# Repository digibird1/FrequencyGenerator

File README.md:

# FrequencyGenerator
Frequency generator based on the LTC9603 Programmable Oscillator and controlled by the ATMEL ATMEGA328 microcontroller (Arduino)
The operation frequency is 1kHz-68MHz

http://www.linear.com/product/LTC6903

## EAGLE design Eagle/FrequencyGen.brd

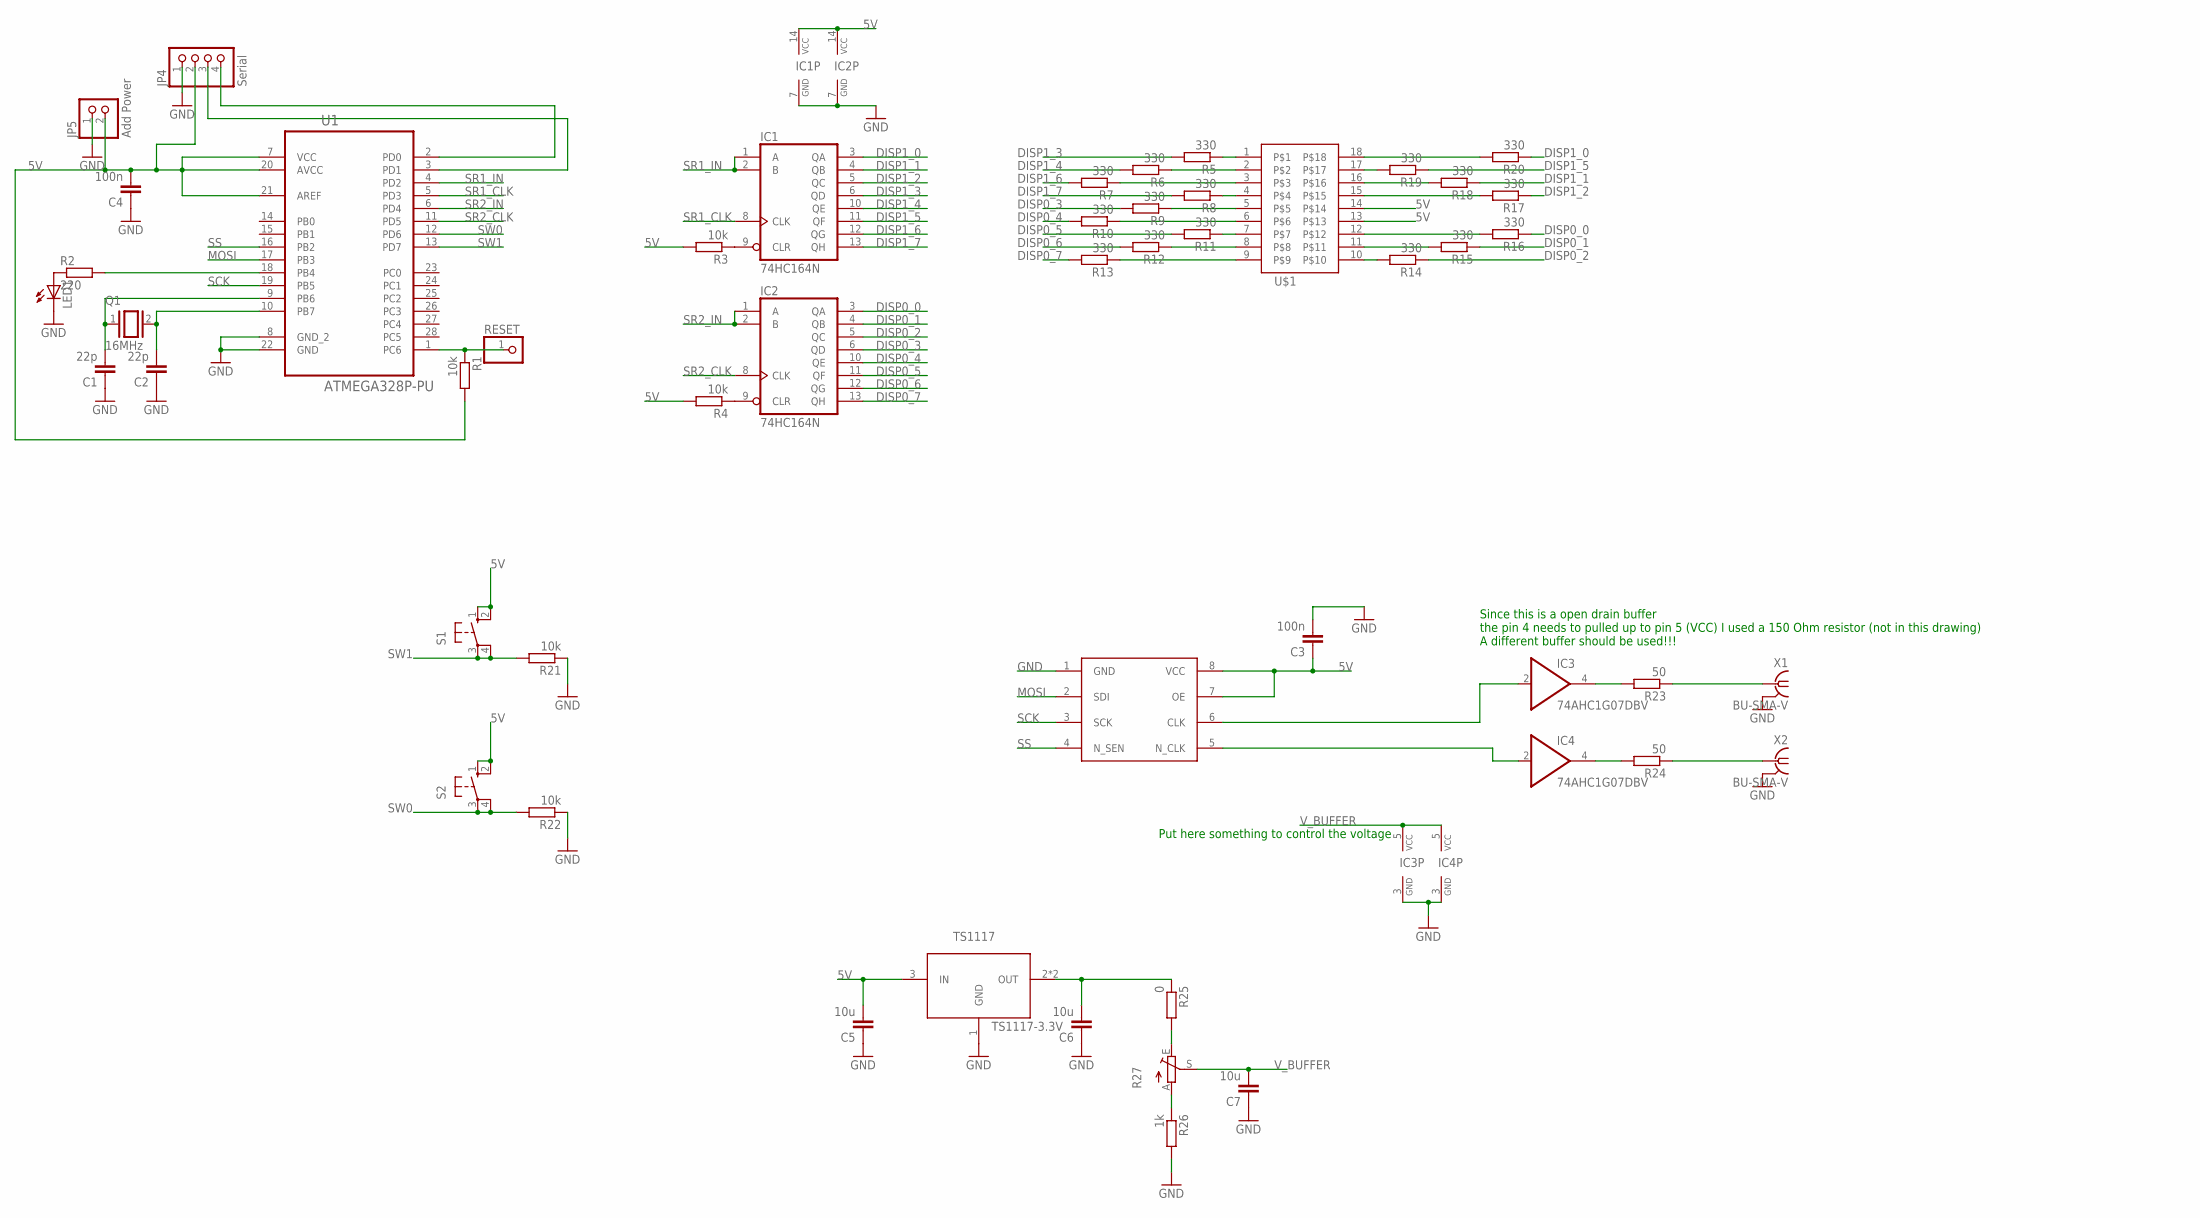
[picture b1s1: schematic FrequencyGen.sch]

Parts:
C1, C2: 22p; C0805
C3, C4: 100n; C0805
C5, C6, C7: 10u; C0805
IC1, IC2: 74HC164N; DIL14
IC3, IC4: 74AHC1G07DBV; SOT23-5
JP4: Serial; 1X04
JP5: Add Power; 1X02
LED1: LED_ELD260; LED_LD260
Q1: 16MHz; QS
R1, R3, R4, R21, R22: 10k; R0805
R2: 220; R0805
R5, R6, R7, R8, R9, R10, R11, R12, R13, R14, R15, R16, R17, R18, R19, R20: 330; R0805
R23, R24: 50; R0805
R25: 0; R0805
R26: 1k; R0805
R27: TRIM_EU-CA6V; CA6V
RESET: PINHD-1X1; 1X01
S1, S2: 10-XX; B3F-10XX
U1: ATMEGA328P-PU; DIP254P762X457-28
U$1: SEG_DISP_2X8; DIL18-6
U$2: LTC6903; MSOP8
U$3: TS1117-3.3V; SOT223
X1, X2: BU-SMA-V

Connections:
5V: C3.1, C4.2, C5.2, IC1.14 (VCC), IC2.14 (VCC), JP4.2, JP5.2, R1.2, R3.2, R4.2, S1.1 (S), S1.2 (S1), S2.1 (S), S2.2 (S1), U1.7 (VCC), U1.20 (AVCC), U1.21 (AREF), U$1.13, U$1.14, U$2.7 (OE), U$2.8 (VCC), U$3.3 (IN)
DISP0_0: IC2.3 (QA), R16.1
DISP0_1: IC2.4 (QB), R15.1
DISP0_2: IC2.5 (QC), R14.1
DISP0_3: IC2.6 (QD), R9.2
DISP0_4: IC2.10 (QE), R10.2
DISP0_5: IC2.11 (QF), R11.2
DISP0_6: IC2.12 (QG), R12.2
DISP0_7: IC2.13 (QH), R13.2
DISP1_0: IC1.3 (QA), R20.1
DISP1_1: IC1.4 (QB), R18.1
DISP1_2: IC1.5 (QC), R17.1
DISP1_3: IC1.6 (QD), R5.2
DISP1_4: IC1.10 (QE), R6.2
DISP1_5: IC1.11 (QF), R19.1
DISP1_6: IC1.12 (QG), R7.2
DISP1_7: IC1.13 (QH), R8.2
GND: C1.1, C2.1, C3.2, C4.1, C5.1, C6.1, C7.1, IC1.7 (GND), IC2.7 (GND), IC3.3 (GND), IC4.3 (GND), JP4.1, JP5.1, LED1.K (C), R21.1, R22.1, R26.2, U1.8 (GND_2), U1.22 (GND), U$2.1 (GND), U$3.1 (GND), X1.2, X1.3 (2), X1.4 (2), X1.5 (2), X2.2, X2.3 (2), X2.4 (2), X2.5 (2)
MOSI: U1.17 (PB3), U$2.2 (SDI)
unnamed: LED1.A, R2.1
unnamed: IC1.9 (CLR), R3.1
unnamed: IC2.9 (CLR), R4.1
unnamed: R5.1, U$1.1
unnamed: R1.1, RESET.1, U1.1 (PC6)
unnamed: C1.2, Q1.1, U1.9 (PB6)
unnamed: C2.2, Q1.2, U1.10 (PB7)
unnamed: R6.1, U$1.2
unnamed: R7.1, U$1.3
unnamed: R8.1, U$1.4
unnamed: R9.1, U$1.5
unnamed: R10.1, U$1.6
unnamed: R11.1, U$1.7
unnamed: R12.1, U$1.8
unnamed: R13.1, U$1.9
unnamed: R20.2, U$1.18
unnamed: R19.2, U$1.17
unnamed: R18.2, U$1.16
unnamed: R17.2, U$1.15
unnamed: R16.2, U$1.12
unnamed: R15.2, U$1.11
unnamed: R14.2, U$1.10
unnamed: R2.2, U1.18 (PB4)
unnamed: JP4.3, U1.3 (PD1)
unnamed: JP4.4, U1.2 (PD0)
unnamed: IC3.4 (O), R23.2
unnamed: IC4.4 (O), R24.2
unnamed: R23.1, X1.1
unnamed: R24.1, X2.1
unnamed: IC3.2 (I), U$2.6 (CLK)
unnamed: IC4.2 (I), U$2.5 (N_CLK)
unnamed: R25.2, R27.E
unnamed: C6.2, R25.1, U$3.2 (OUT), U$3.4 (OUT)
unnamed: R26.1, R27.A
SCK: U1.19 (PB5), U$2.3 (SCK)
SR1_CLK: IC1.8 (CLK), U1.5 (PD3)
SR1_IN: IC1.1 (A), IC1.2 (B), U1.4 (PD2)
SR2_CLK: IC2.8 (CLK), U1.11 (PD5)
SR2_IN: IC2.1 (A), IC2.2 (B), U1.6 (PD4)
SS: U1.16 (PB2), U$2.4 (N_SEN)
SW0: R22.2, S2.3, S2.4 (P1), U1.12 (PD6)
SW1: R21.2, S1.3, S1.4 (P1), U1.13 (PD7)
V_BUFFER: C7.2, IC3.5 (VCC), IC4.5 (VCC), R27.S

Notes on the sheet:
Put here something to control the voltage
Since this is a open drain buffer the pin 4 needs to pulled up to pin 5 (VCC) I used a 150 Ohm resistor (not in this drawing) A different buffer should be used!!!

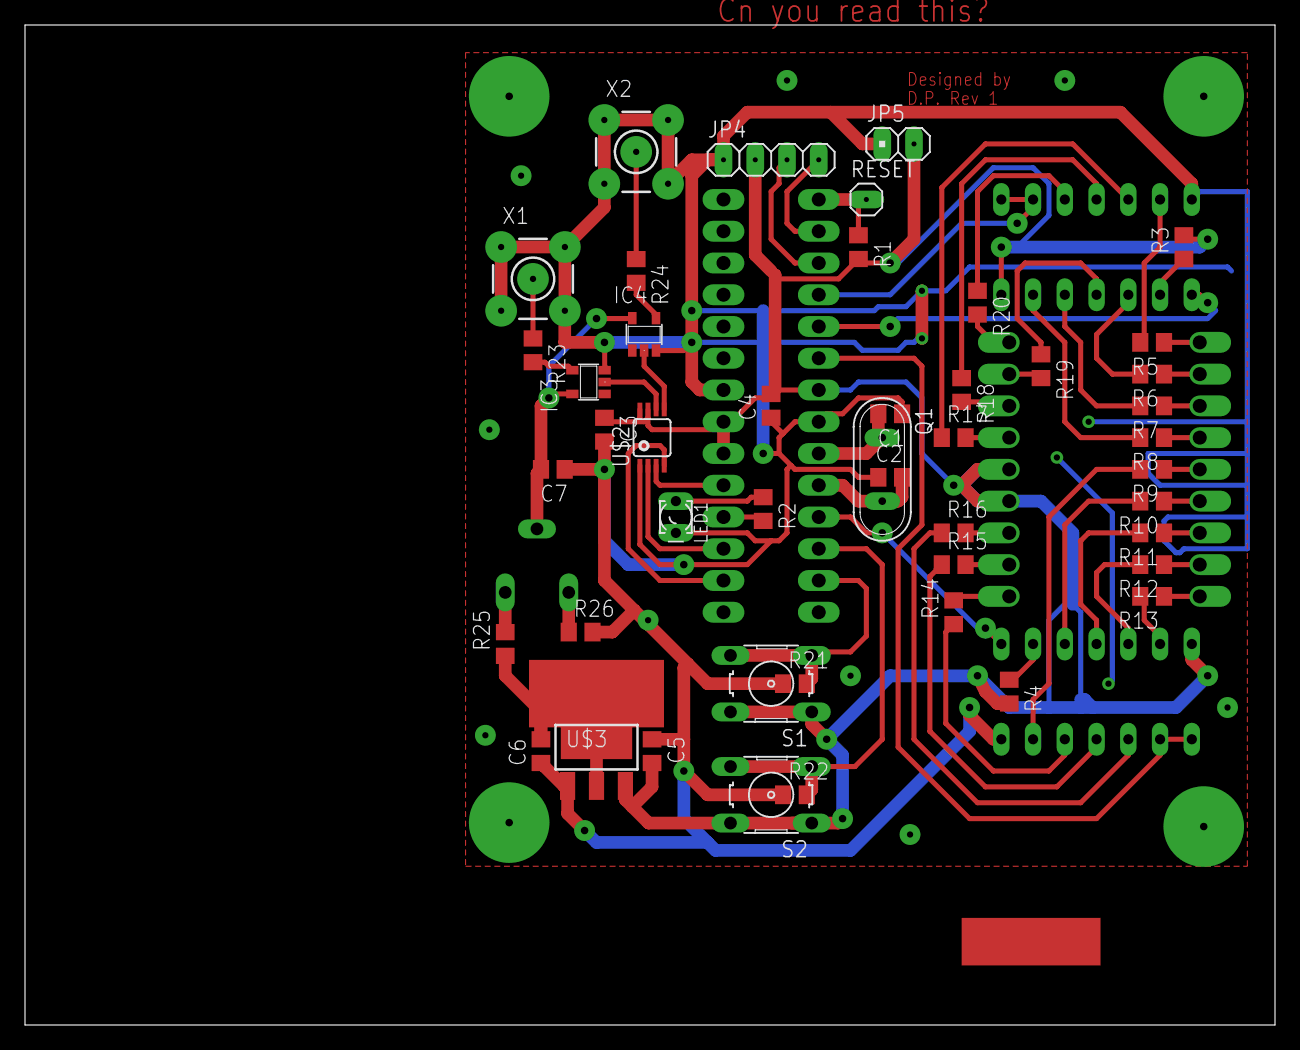
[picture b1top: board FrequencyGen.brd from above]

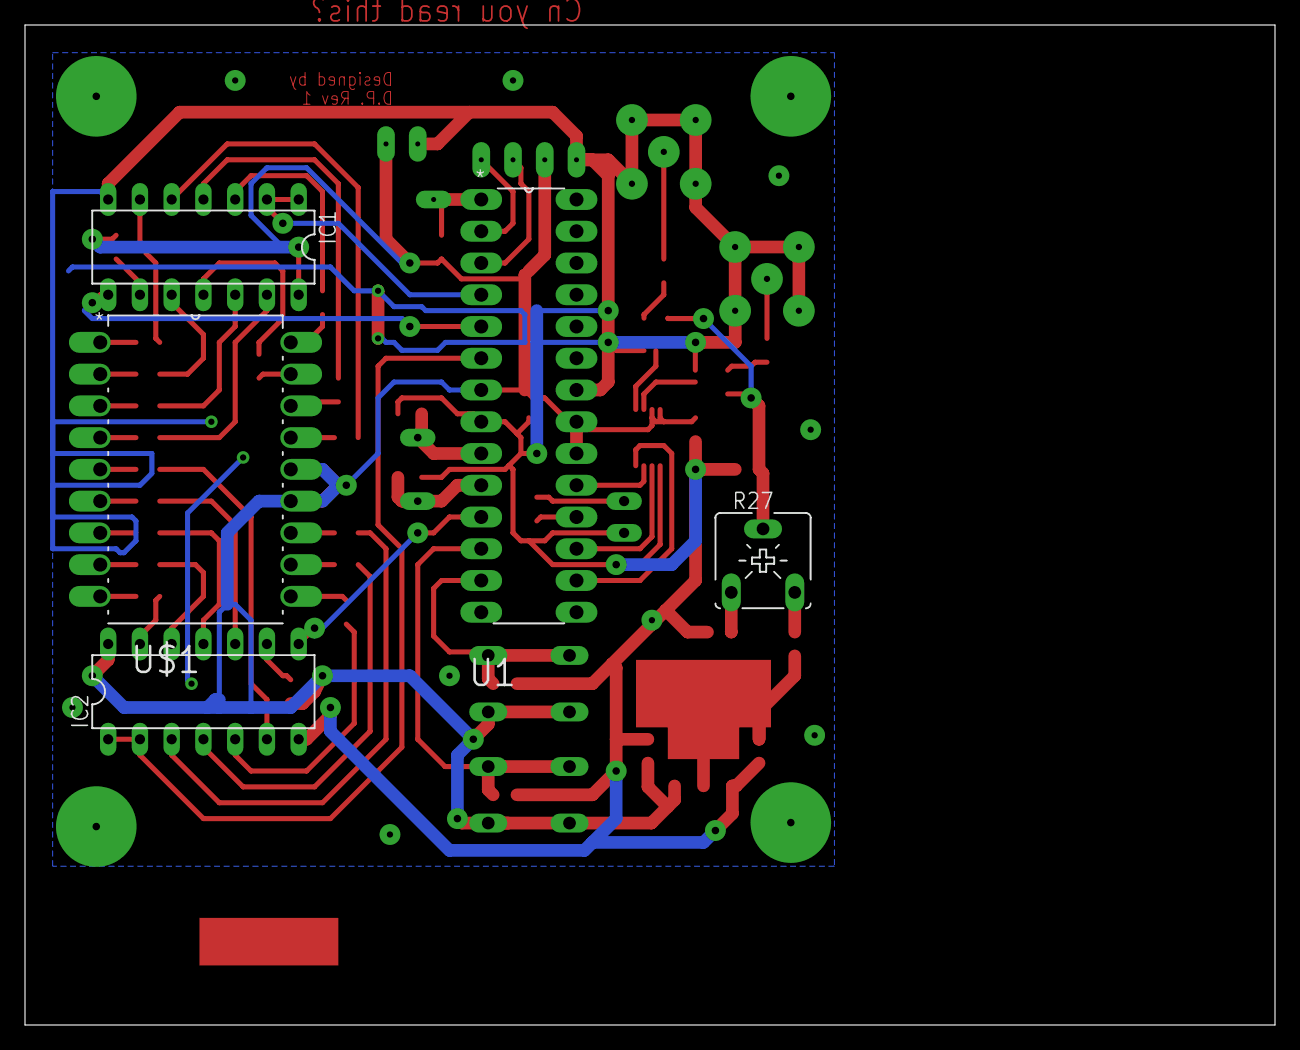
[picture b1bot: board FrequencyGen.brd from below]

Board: 2 copper layers, 100.0 x 80.0 mm, 51 parts (5 on the bottom side), 62 nets.

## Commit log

2015-04-01 Eagle PCB files and Source Code
